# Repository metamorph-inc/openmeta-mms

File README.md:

# OpenMETA Source Repository #
OpenMETA is an integrated, open-source, model-based platform used to design and analyze complex systems, such as spacecraft, automobiles, aircraft, and electronics.

This repository is a fork of OpenMETA that includes extensions developed by MetaMorph, Inc.

The core OpenMETA codebase is available here:
https://github.com/metamorph-inc/meta-core

## Obtaining OpenMETA
The easiest way to get started with OpenMETA is to download an installer for Windows. OpenMETA installers for Windows are frequently released by MetaMorph, Inc at their website:
https://openmeta.metamorphsoftware.com/

To build OpenMETA from source, see **[BUILD.md](BUILD.md)**.

## Documentation and Examples
User documentation for OpenMETA is hosted by MetaMorph, Inc at:
http://docs.metamorphsoftware.com 

The documentation includes:
* Concept Introduction
* Walkthroughs
* Details of specific tool integrations

Case Studies
* OpenMETA for Electronics Design
  * Live Presentation and Demonstration: https://www.youtube.com/watch?v=KghND-sZ0s4
* Vahana Trade Study _(aerospace)_. Autonomous transport vehicle.
  * Report: https://www.metamorphsoftware.com/blog/2017/8/31/openmeta-vahana-case-study-part-i
  * Project: https://github.com/metamorph-inc/openmeta-vahana
* Spacecraft Trade Study
  * Quick Tour Video: https://www.youtube.com/watch?v=OHrgiL06z2s
  * Project: https://github.com/metamorph-inc/openmeta-spacecraft-study

## License
OpenMETA is distributed under the MIT open-source license. See **[license.txt](license.txt)**

This repository is a fork of OpenMETA that includes extensions developed by MetaMorph, Inc.

The core OpenMETA codebase is available here:
https://github.com/metamorph-inc/meta-core

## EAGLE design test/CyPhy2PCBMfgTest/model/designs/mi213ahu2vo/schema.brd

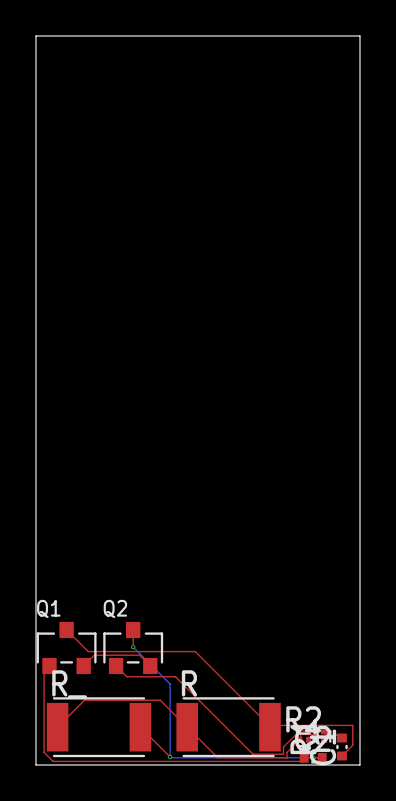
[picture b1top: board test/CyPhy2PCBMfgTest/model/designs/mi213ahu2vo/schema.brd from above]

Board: 2 copper layers, 18.0 x 40.5 mm, 8 parts (0 on the bottom side), 6 nets.

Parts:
C1, C2: C0402
Q1, Q2: TRANSISTOR_NPN_SOT23; SOT23
R: RESISTOR_2010; R_2010
R1, R2: RESISTOR_0201; R_0201
R_: RESISTOR_2010; R_2010

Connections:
unnamed: C2.1, Q1.B, R2.P$2
unnamed: C2.2, Q2.C, R_.P$2
unnamed: R.P$1, R1.P$1, R2.P$1, R_.P$1
unnamed: C1.2, Q2.B, R1.P$2
unnamed: C1.1, Q1.C, R.P$2
unnamed: Q1.E, Q2.E

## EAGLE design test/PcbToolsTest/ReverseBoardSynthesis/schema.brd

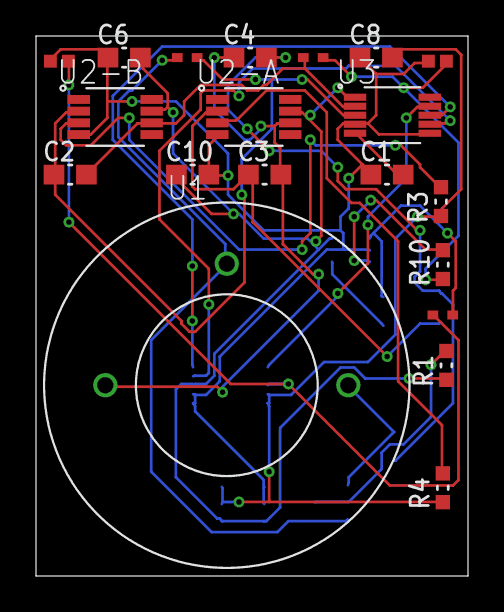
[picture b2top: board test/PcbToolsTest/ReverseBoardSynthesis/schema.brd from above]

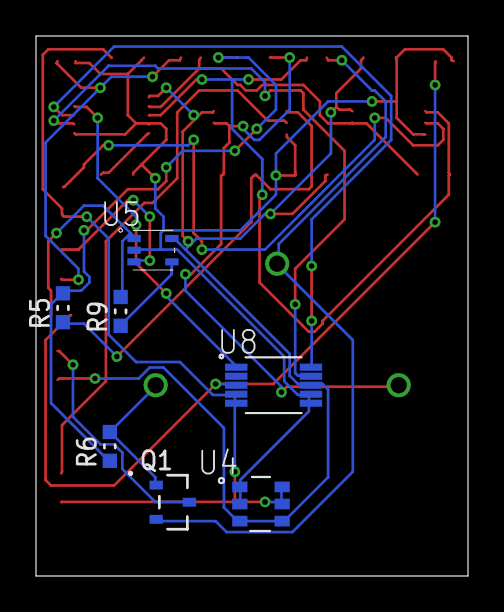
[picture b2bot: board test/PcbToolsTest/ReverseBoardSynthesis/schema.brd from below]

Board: 2 copper layers, 24.0 x 30.0 mm, 27 parts (7 on the bottom side), 22 nets.

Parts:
C1, C6: TMK107B7105KA-T; C_0603
C2, C3, C4: CL10B203KB8NNNC; C_0603
C8, C10: GCM188R71E104KA57D; C_0603
C9: C1005X5R0J106M050BC; C_0402
C14: CL05B562KB5NNNC; C_0402
Q1: MMBFJ270; SOT23-3
R1: CR0603-JW-105ELF; R_0603
R2: ERJ-2GEJ330X; R_0402
R3, R4, R5, R6: RT0603DRD0712K4L; R_0603
R8: ESR01MZPJ104; R_0402
R9, R10: CRCW06033K30JNEA; R_0603
R12: ERJ-2GEJ151X; R_0402
U1: CO-AX
U2-A, U2-B: ADA4528-2ARMZ; MSOP-8
U3: AD5270BRMZ-20; MSOP-10
U4: AD3412ARJZ; SOT-23
U5: AD8500AKSZ-R2; SC-70
U8: AD7790BRMZ; MSOP-10

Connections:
unnamed: C1.1, C6.1, C8.1, C9.1, C10.2, C14.1, U2-A.P$4, U2-B.P$4, U3.P$4, U3.P$6, U4.P$1, U4.P$2, U5.P$2, U8.P$6, U8.P$7
unnamed: C1.2, U3.P$5
unnamed: C6.2, C10.1, R1.P$1, U2-A.P$7, U2-B.P$7, U3.P$1, U4.P$3, U4.P$4, U5.P$5, U8.P$8
unnamed: C14.2, R12.P$1, U8.P$3
unnamed: C2.2, R8.P$1, U2-B.P$6, U3.P$2
unnamed: C2.1, R2.P$2, U2-B.P$2, U3.P$3
unnamed: C3.2, C4.1, U1.COUNTER, U2-A.P$6
unnamed: C3.1, R5.P$1, U2-A.P$2
unnamed: C4.2, R5.P$2, R6.P$1
unnamed: C8.2, R3.P$1, R4.P$1, U4.P$5, U4.P$6, U8.P$4, U8.P$5
unnamed: C9.2, R8.P$2, R10.P$1
unnamed: Q1.1, R6.P$2, U1.REFERENCE
unnamed: Q1.2, R2.P$1, U1.WORKER
unnamed: Q1.3, R1.P$2
unnamed: R10.P$2, U5.P$3
unnamed: R9.P$2, R12.P$2, U5.P$1
unnamed: R3.P$2, U2-B.P$3
unnamed: R4.P$2, U2-A.P$3
unnamed: R9.P$1, U5.P$4
unnamed: U3.P$9, U8.P$1
unnamed: U3.P$8, U8.P$10
unnamed: U3.P$7, U8.P$9

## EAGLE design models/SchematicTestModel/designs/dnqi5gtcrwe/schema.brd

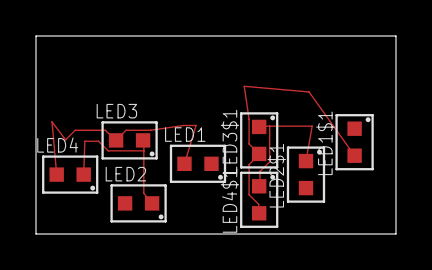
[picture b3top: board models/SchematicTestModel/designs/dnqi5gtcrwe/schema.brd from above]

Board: 2 copper layers, 20.0 x 11.0 mm, 8 parts (0 on the bottom side), 4 nets.

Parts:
LED1, LED1$1, LED2, LED2$1, LED3, LED3$1, LED4, LED4$1: LTST-C191KRKT; LED

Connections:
unnamed: LED2.CATHODE, LED3.CATHODE, LED4.CATHODE
unnamed: LED1.ANODE, LED3.ANODE, LED4.ANODE
unnamed: LED2$1.CATHODE, LED3$1.CATHODE, LED4$1.CATHODE
unnamed: LED1$1.ANODE, LED3$1.ANODE, LED4$1.ANODE

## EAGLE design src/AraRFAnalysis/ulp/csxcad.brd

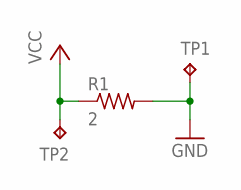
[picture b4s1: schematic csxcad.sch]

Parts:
R1: 2; R0603
TP1, TP2: TPB2,54; B2,54

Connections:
GND: R1.2, TP1.TP
VCC: R1.1, TP2.TP

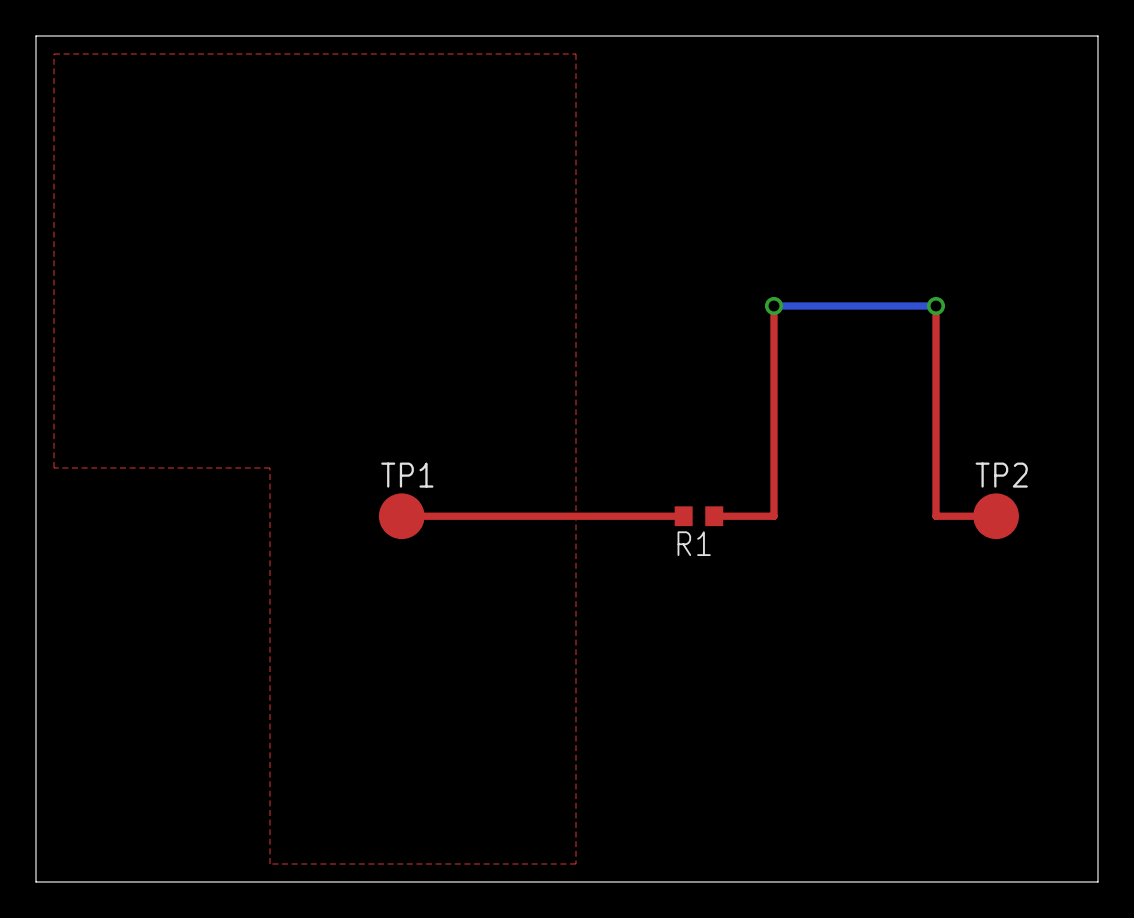
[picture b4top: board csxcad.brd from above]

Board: 2 copper layers, 59.0 x 47.0 mm, 3 parts (0 on the bottom side), 2 nets.

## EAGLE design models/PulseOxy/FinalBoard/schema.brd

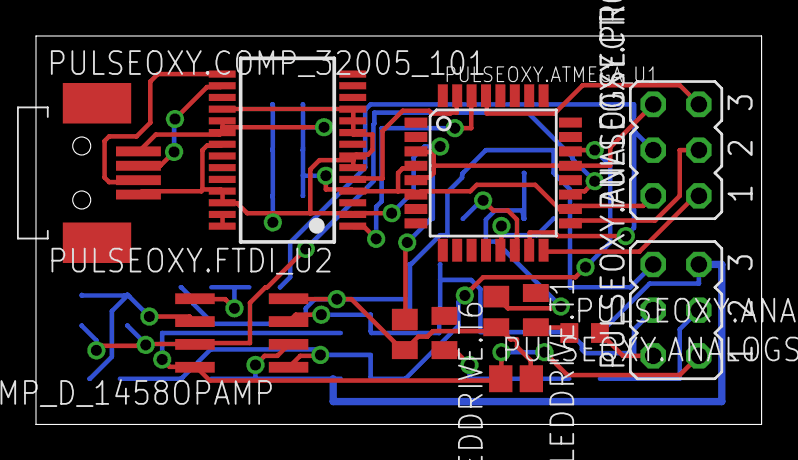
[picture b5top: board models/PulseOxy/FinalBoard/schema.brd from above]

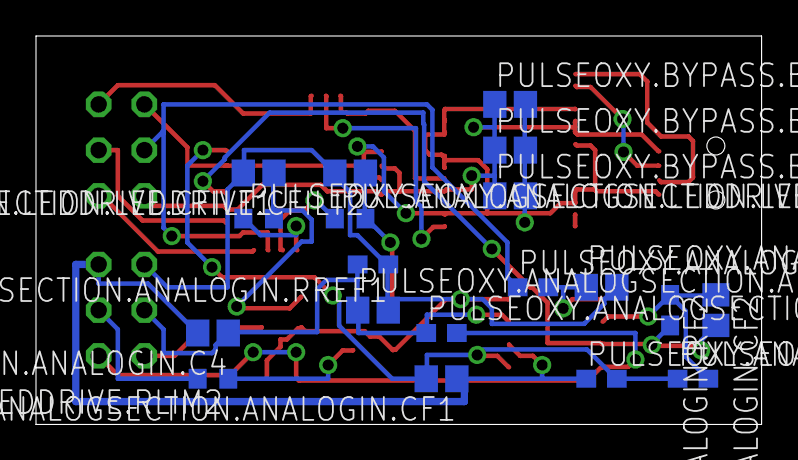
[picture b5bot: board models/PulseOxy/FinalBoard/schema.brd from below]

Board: 2 copper layers, 40.3 x 21.6 mm, 29 parts (19 on the bottom side), 27 nets.

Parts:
PULSEOXY.ANALOGSECTION.ANALOGIN.C2, PULSEOXY.ANALOGSECTION.ANALOGIN.C4, PULSEOXY.ANALOGSECTION.ANALOGIN.CBP1, PULSEOXY.ANALOGSECTION.ANALOGIN.CF1, PULSEOXY.ANALOGSECTION.ANALOGIN.CF2, PULSEOXY.ANALOGSECTION.ANALOGIN.CREF, PULSEOXY.ANALOGSECTION.LEDDRIVE.CFILT1, PULSEOXY.ANALOGSECTION.LEDDRIVE.CFILT2, PULSEOXY.BYPASS.BP1, PULSEOXY.BYPASS.BP2, PULSEOXY.BYPASS.BP3: C0805
PULSEOXY.ANALOGSECTION.ANALOGIN.COMP_D_1458OPAMP: LM1458D; SO08
PULSEOXY.ANALOGSECTION.ANALOGIN.R11, PULSEOXY.ANALOGSECTION.ANALOGIN.RF1, PULSEOXY.ANALOGSECTION.ANALOGIN.RF2, PULSEOXY.ANALOGSECTION.ANALOGIN.RI2, PULSEOXY.ANALOGSECTION.ANALOGIN.RREF1, PULSEOXY.ANALOGSECTION.ANALOGIN.RREF2: C0603
PULSEOXY.ANALOGSECTION.LEDDRIVE.RDRIVE1, PULSEOXY.ANALOGSECTION.LEDDRIVE.RDRIVE2, PULSEOXY.ANALOGSECTION.LEDDRIVE.RLIM1, PULSEOXY.ANALOGSECTION.LEDDRIVE.RLIM2: R0603
PULSEOXY.ANALOGSECTION.LEDDRIVE.T1, PULSEOXY.ANALOGSECTION.LEDDRIVE.T6: SOT143
PULSEOXY.ANALOGSECTION.SENSORHEADER, PULSEOXY.PROGRPORT: JP3Q
PULSEOXY.ATMEGA_U1: MEGA48/88/168-AU; TQFP32-08
PULSEOXY.COMP_32005_101: MINI-USB_4P-32005-101; 32005-101
PULSEOXY.FTDI_U2: FT232RL; SSOP28

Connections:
unnamed: PULSEOXY.ANALOGSECTION.ANALOGIN.C2.2, PULSEOXY.ANALOGSECTION.ANALOGIN.CBP1.2, PULSEOXY.ANALOGSECTION.ANALOGIN.COMP_D_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.4, PULSEOXY.ANALOGSECTION.ANALOGIN.CREF.2, PULSEOXY.ANALOGSECTION.ANALOGIN.RREF1.1, PULSEOXY.ANALOGSECTION.LEDDRIVE.CFILT1.2, PULSEOXY.ANALOGSECTION.LEDDRIVE.CFILT2.2, PULSEOXY.ANALOGSECTION.LEDDRIVE.T1.2, PULSEOXY.ANALOGSECTION.LEDDRIVE.T6.2, PULSEOXY.ANALOGSECTION.SENSORHEADER.6
unnamed: PULSEOXY.ANALOGSECTION.ANALOGIN.C2.1, PULSEOXY.ANALOGSECTION.ANALOGIN.COMP_D_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.5, PULSEOXY.ANALOGSECTION.ANALOGIN.R11.2
unnamed: PULSEOXY.ANALOGSECTION.ANALOGIN.C4.2, PULSEOXY.ANALOGSECTION.ANALOGIN.CF1.1, PULSEOXY.ANALOGSECTION.ANALOGIN.COMP_D_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.2, PULSEOXY.ANALOGSECTION.ANALOGIN.RF1.1, PULSEOXY.ANALOGSECTION.SENSORHEADER.5
unnamed: PULSEOXY.ANALOGSECTION.ANALOGIN.C4.1, PULSEOXY.ANALOGSECTION.ANALOGIN.COMP_D_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.3, PULSEOXY.ANALOGSECTION.ANALOGIN.CREF.1, PULSEOXY.ANALOGSECTION.ANALOGIN.RREF1.2, PULSEOXY.ANALOGSECTION.ANALOGIN.RREF2.1, PULSEOXY.ANALOGSECTION.SENSORHEADER.4
unnamed: PULSEOXY.ANALOGSECTION.ANALOGIN.CBP1.1, PULSEOXY.ANALOGSECTION.ANALOGIN.COMP_D_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.8, PULSEOXY.ANALOGSECTION.ANALOGIN.RREF2.2, PULSEOXY.ANALOGSECTION.SENSORHEADER.1
unnamed: PULSEOXY.ANALOGSECTION.ANALOGIN.CF1.2, PULSEOXY.ANALOGSECTION.ANALOGIN.COMP_D_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.1, PULSEOXY.ANALOGSECTION.ANALOGIN.RF1.2, PULSEOXY.ANALOGSECTION.ANALOGIN.RI2.1, PULSEOXY.ATMEGA_U1.22
unnamed: PULSEOXY.ANALOGSECTION.ANALOGIN.CF2.2, PULSEOXY.ANALOGSECTION.ANALOGIN.COMP_D_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.7, PULSEOXY.ANALOGSECTION.ANALOGIN.RF2.2, PULSEOXY.ATMEGA_U1.19
unnamed: PULSEOXY.ANALOGSECTION.ANALOGIN.CF2.1, PULSEOXY.ANALOGSECTION.ANALOGIN.COMP_D_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.6, PULSEOXY.ANALOGSECTION.ANALOGIN.RF2.1, PULSEOXY.ANALOGSECTION.ANALOGIN.RI2.2
unnamed: PULSEOXY.ANALOGSECTION.ANALOGIN.R11.1, PULSEOXY.ATMEGA_U1.15, PULSEOXY.PROGRPORT.4
unnamed: PULSEOXY.ANALOGSECTION.LEDDRIVE.CFILT1.1, PULSEOXY.ANALOGSECTION.LEDDRIVE.RDRIVE1.2, PULSEOXY.ANALOGSECTION.LEDDRIVE.T1.1
unnamed: PULSEOXY.ANALOGSECTION.LEDDRIVE.CFILT2.1, PULSEOXY.ANALOGSECTION.LEDDRIVE.RDRIVE2.2, PULSEOXY.ANALOGSECTION.LEDDRIVE.T6.1
unnamed: PULSEOXY.ANALOGSECTION.LEDDRIVE.RDRIVE1.1, PULSEOXY.ATMEGA_U1.13
unnamed: PULSEOXY.ANALOGSECTION.LEDDRIVE.RDRIVE2.1, PULSEOXY.ATMEGA_U1.14
unnamed: PULSEOXY.ANALOGSECTION.LEDDRIVE.RLIM1.2, PULSEOXY.ANALOGSECTION.SENSORHEADER.2
unnamed: PULSEOXY.ANALOGSECTION.LEDDRIVE.RLIM1.1, PULSEOXY.ANALOGSECTION.LEDDRIVE.T1.3
unnamed: PULSEOXY.ANALOGSECTION.LEDDRIVE.RLIM2.1, PULSEOXY.ANALOGSECTION.LEDDRIVE.T6.3
unnamed: PULSEOXY.ANALOGSECTION.LEDDRIVE.RLIM2.2, PULSEOXY.ANALOGSECTION.SENSORHEADER.3
unnamed: PULSEOXY.ATMEGA_U1.4, PULSEOXY.ATMEGA_U1.6, PULSEOXY.ATMEGA_U1.18, PULSEOXY.BYPASS.BP1.1, PULSEOXY.BYPASS.BP2.1, PULSEOXY.BYPASS.BP3.1, PULSEOXY.COMP_32005_101.1, PULSEOXY.FTDI_U2.4, PULSEOXY.FTDI_U2.19, PULSEOXY.FTDI_U2.20, PULSEOXY.PROGRPORT.2
unnamed: PULSEOXY.ATMEGA_U1.3, PULSEOXY.ATMEGA_U1.5, PULSEOXY.ATMEGA_U1.21, PULSEOXY.BYPASS.BP1.2, PULSEOXY.BYPASS.BP2.2, PULSEOXY.BYPASS.BP3.2, PULSEOXY.COMP_32005_101.4, PULSEOXY.FTDI_U2.2, PULSEOXY.FTDI_U2.6, PULSEOXY.FTDI_U2.7, PULSEOXY.FTDI_U2.9, PULSEOXY.FTDI_U2.10, PULSEOXY.FTDI_U2.11, PULSEOXY.FTDI_U2.18, PULSEOXY.FTDI_U2.21, PULSEOXY.FTDI_U2.25, PULSEOXY.FTDI_U2.26, PULSEOXY.PROGRPORT.6
unnamed: PULSEOXY.ATMEGA_U1.30, PULSEOXY.FTDI_U2.1
unnamed: PULSEOXY.ATMEGA_U1.31, PULSEOXY.FTDI_U2.5
unnamed: PULSEOXY.ATMEGA_U1.29, PULSEOXY.PROGRPORT.5
unnamed: PULSEOXY.ATMEGA_U1.16, PULSEOXY.PROGRPORT.1
unnamed: PULSEOXY.ATMEGA_U1.17, PULSEOXY.PROGRPORT.3
unnamed: PULSEOXY.COMP_32005_101.3, PULSEOXY.FTDI_U2.15
unnamed: PULSEOXY.COMP_32005_101.2, PULSEOXY.FTDI_U2.16
unnamed: PULSEOXY.FTDI_U2.27, PULSEOXY.FTDI_U2.28

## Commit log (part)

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2017-11-21 Update Python dependencies (for MATLAB bare file support)
2017-11-22 OPENMETA-329 Added table of conversions to MATLAB docs.
2017-11-27 OPENMETA-329 Added CSS fix for 'code-block' caption permalinks.
2017-11-29 OPENMETA-332 add documentation for including and excluding specific test benches with the Continuous Integration script
2017-11-29 RunTestBenches: support PETs
2017-11-30 RunTestBenches: check PET MetricConstraints in all hierarchy and all runs
2017-11-30 OPENMETA-335 Updated MATLAB/OpenMDAO mapping table.
2017-12-01 Updated Continuous Integration Docs.
2017-12-04 Remote execution skeleton code
2017-12-07 More implementation of remote job mananger support; test project for remote job manager support (and placeholder for other PET tests)
2017-12-11 OPENMETA-346 Start Adding CAD Documentation.
2017-12-11 OPENMETA-346 Finish initial cut at CAD Documentation.
2017-12-13 Fix broken links to documentation in BUILD.md
2017-12-13 SimulinkImporter test fixture: don't crash if MATLAB isn't installed
2017-12-14 Prompt for remote server username and password
2017-12-14 UI tweak to remote server dialog
2017-12-15 Add CATIA to CADModel.FileFormat
2018-01-02 OPENMETA-357 General cleanup of existing code.
2018-01-03 OPENMETA-357 Fix naming convention of functions.
2018-01-03 OPENMETA-357 Fix xunit reference errors.
2018-01-04 OPENMETA-357 Set Abort to false in InvokeEx.
2018-01-05 OPENMETA-357 Added new Merge Connectors code.
2018-01-05 OPENMETA-357 Fixed Merge behaviour.
2018-01-05 Consider any 'complete' status where _FAILED.txt is present to be a failure (matches LocalPool behavior); reorder status check so that Test Benches tab updates after we've downloaded results
2018-01-08 OPENMETA-357 Refactored SpiceImportWithPinMatch() test.
    1. Reverted ComponentAuthoringTool.xme.
    2. Added Generator library and device.
    3. Import generator device before spice import.
2018-01-09 OPENMETA-349 Improvements to CustomProcessor.py
2018-01-10 OPENMETA-360 Recently used server list in remote server connection dialog
2018-01-12 OPENMETA-349 Added documentation for Custom Processor.
2018-01-12 OPENMETA-348 Add picture of CSV File DOE Type Configuration.
2018-01-12 Populate remote job labels with labels from interpreters
2018-01-13 OPENMETA-349 Added new operators to ValueAggregator.py
    Added COUNT, AVERAGE, MIN, MAX, AND, OR
    Augmented the documentation to include the new operators.
2018-01-15 Fixed preparepublish.bat script to point to META Python.
2018-01-19 OPENMETA-362 Use Python path from registry for Simulink test bench execution
2018-01-22 TestRemoteExecution: don't depend on xunit, it is not in the installer. OPENMETA-384
2018-01-22 TestRemoteExecution: add more labels
2018-01-23 OPENMETA-391 Add SPICETest TB to SchematicUnitTests.
2018-01-23 Upgrade to v2.0.0 of openmeta-visualizer.
2018-01-23 OPENMETA-356 Handle remote executor cancellation requested status
2018-01-24 OPENMETA-371 Added sections on Job Labels and Remote Job Statuses.
2018-01-25 One more case where a right-click item could be invoked with no selected item
2018-01-26 OPENMETA-371 some formatting on Test Benches first page
2018-01-26 OPENMETA-371 Updated definitions of test bench.
2018-01-30 Add tonka-specific Jenkinsfile
2018-01-30 Changed docs to draw version number from git tag.
2018-01-31 Use full artifact path for unarchive command
2018-01-31 Adjust cache behavior on root website objects
2018-01-31 Psuedo-release 0.18.2
2018-02-01 OPENMETA-410 Change ToC title from 'Caption' to 'Sections'.
2018-02-01 docs/make: Fail on error
2018-02-01 Fix syntax of s3Upload command
2018-02-01 Use path without / prefix to delete and upload docs
2018-02-05 OPENMETA-413 Added new docs chapters into index.
2018-02-06 OPENMETA-413 Fix broken master interpreter reference.
2018-02-06 OPENMETA-413 Some minor changes to docs to prepare stubs for contributions.
2018-02-07 OPENMETA-418 Initial draft for OpenMETA projects Chapter.
2018-02-08 OPENMETA-425 Master Interpreter Docs
2018-02-08 OPENMETA-426 Create new See It In Action chapter. Move Hello World.
2018-02-09 OPENMETA-417 Completed Hello World tutorial and added hello_world OpenMETA project.
2018-02-09 Testbenches: re-add Workflows under 'AraTestBenches' since some models depend on them
2018-02-09 CyPhy2MfgBom: properly close log file instead of relying on finalizer
2018-02-09 OPENMETA-420 Move Component Composition section to Component Assemblies chapter.
2018-02-09 Don't need matlab.pth; MATLAB python is added by matlab_wrapper
2018-02-12 OPENMETA-430 Switching to using menuselection directive.
2018-02-12 Fixed typos found in OpenMETA Projects chapter & added a more detailed description of the example .gitignore file
2018-02-14 Corrected Typos and clarified some wording in LED Tutorial, Components, Design Spaces, Domains, and Interpreters chapters
2018-02-16 Fixed typos and a naming issue in PET Tutorial
2018-02-16 Typos and wording corrected in Utilities chapter
2018-02-19 OPENMETA-422 Added note about enabling interpreter buttons.
2018-02-19 Added clarification to LED Tutorial and fixed typos in Integrated Domain section
2018-02-20 OPENMETA-338 Adjust docs to reflect tested MATLAB compatibility.
2018-02-20 OPENMETA-417 Revert a couple small changes.
2018-02-21 Changed all 'Contents:' to 'Sections'
2018-02-21 OPENMETA-417 Renamed test bench references/links.
2018-02-21 OPENMETA-417 Fixed broken link.
2018-02-21 OPENMETA-423 Revised Test Bench chapter of documentation.
2018-02-21 OPEMNETA-419 add tutorial on Class Inheritance for Component Authoring
2018-02-23 Updated final few PET Tutorial Screenshots and fixed a broken reference in OpenMETA Projects
2018-02-23 OPENMETA-423 Fixed typos in Test Benches chapter
2018-02-26 OPENMETA-419 Updated images in Inheritance tutorial to comply with Documentation style guide
2018-02-26 Fixed typos throughout, and clarified sections of the FEA tutorial in Integrated Domains
2018-02-27 OPENMETA-417 added missing reference anchor link.
2018-02-28 Jenkins: only build CAD if it is not on nuget
2018-02-28 OPENMETA-416 Images updated and clarification added in PET Reference
2018-03-02 OPENMETA-428 Fixed broken sentence regarding Python wrappers in PET Reference
2018-03-02 OPENMETA-428 Duplicated conceptual LED Component drawing in the Components chapter for clarity
2018-03-02 OPENMETA-428 Fixed references to the FEA tutorial example files
2018-03-28 Remove dup pywin32
2018-03-29 Port over old PCC docs (without images for now)
2018-03-30 Rename installer for easier version tracking
2018-04-04 OPENMETA-485 Minor formatting changes.
2018-04-04 More icons and layout fixes
2018-04-05 API changes to allow CAT modules to support execution within ComponentAssemblies
2018-04-05 Fix SchematicUnitTests to use new CAT tool API
2018-04-05 Remove unused CAT icons
2018-04-06 Put some tonka Python packages into zip for installer
2018-04-11 Update copyright dates
2018-04-25 CyPhy2Schematic: add onlyConsiderExactConstraints workflow option
2018-06-08 Add library picker to Simulink CAT
2018-06-13 OPENMETA-476 Check that results folders exist before attempting to watch them for changes when launching visualizer
2018-06-22 Release notes for v0.18.5
2018-06-26 Don't do checkout -b master since the branch already exists and Git apparently doesn't like it when you do that
2018-06-26 Addition of Included Tools section.
2018-06-26 Further improved Installation instructions.
2018-06-27 OPENMETA-517 Prepare for 0.18.6 release.
2018-06-27 Update to point to new OpenMETA homepage
2018-06-28 OPENMETA-517 Constrain images sizes on installation page.
2018-06-28 Release notes for v0.18.7.
2018-07-12 OPENMETA-528 Make PETBrowser SingleInstanceManager per-user
2018-07-27 OPENMETA-530 Show open dialog if there's no results folder to load at the selected location
2018-07-30 OPENMETA-537 Restructured Analysis Blocks Chapters.
2018-08-28 Release notes for v0.19.1.
2018-10-02 Modify documentation to reflect new OpenModelica version (1.12) OPENMETA-558
2018-10-16 Fix botched merge
2018-10-26 Some minor documentation improvements and typo fixes.
2018-10-26 Added another entry to release notes.
2018-11-21 remote_execution /build/: accept job names with dashes
2019-01-04 Add mgardf
2019-01-08 Release v0.21.1; repackaging 0.21.0 due to issue with merge commit on release branch
2019-02-04 Revert accidental change to paraboloid.py
2019-04-23 Remove CyPhy2MfgBom from docs
2019-07-02 Decorator: look for icons where libraries are. OPENMETA-615
2019-07-03 Correct company name in license
2019-09-13 Add one more thing to 0.21.3 release notes
2019-09-16 run_mdao: add --profile command line flag (enables OpenMDAO instance-based profiling)
2019-11-02 Bump request from 2.33.0 to 2.88.0 in /bin/cad.js
    Bumps [request](https://github.com/request/request) from 2.33.0 to 2.88.0.
    - [Release notes](https://github.com/request/request/releases)
    - [Changelog](https://github.com/request/request/blob/master/CHANGELOG.md)
    - [Commits](https://github.com/request/request/compare/v2.33.0...v2.88.0)
2020-01-29 Upgrade to OpenMETA Visualizer v2.1.8.
2020-02-17 Revert "OPENMETA-677 Normalize PYTHONPATH and PYTHONHOME when running jobs in job manager"
    This reverts commit f6d11a2a7198d5a2a4709d7ca9e9fec48a576321.
2020-02-24 Partially functional progress feedback server
2020-02-26 Fix unintentional commit of unresolved conflicted requirements file
2020-02-26 Document progress feedback service protocol; add dependencies to THIRD_PARTY.md
2020-02-29 Upgrade to Visualizer v2.1.10
2020-03-04 Add unsaved release notes
2020-03-30 Set GenericDomainModelParameter icon and portIcon. OPENMETA-717
2020-04-13 Add visualizer export scripts
2020-04-27 Update Meta-Link Java-dependency information
2020-05-05 Fix CyPhy2PCBMfg relying on current working directory
2020-05-21 Allow exported visualizer packages to run under visualizer when installed per-user
2020-07-02 Add list of PET folders to results browser, and ability to navigate directly to them
2020-08-20 Bump bcrypt from 1.0.2 to 5.0.0 in /src/remote_execution
    Bumps [bcrypt](https://github.com/kelektiv/node.bcrypt.js) from 1.0.2 to 5.0.0.
    - [Release notes](https://github.com/kelektiv/node.bcrypt.js/releases)
    - [Changelog](https://github.com/kelektiv/node.bcrypt.js/blob/master/CHANGELOG.md)
    - [Commits](https://github.com/kelektiv/node.bcrypt.js/compare/v1.0.2...v5.0.0)
2020-11-25 Add temporary notice regarding Autodesk EAGLE
2021-03-29 v0.23.0 release notes (WIP)
2021-04-02 Added GME update to release notes
2021-04-26 Bump commons-io from 2.4 to 2.7 in /src/MetaLink/meta-bridge
    Bumps commons-io from 2.4 to 2.7.
2021-06-07 Bump logback-classic from 1.0.13 to 1.2.0 in /src/MetaLink/meta-bridge
    Bumps logback-classic from 1.0.13 to 1.2.0.
    ---
    updated-dependencies:
    - dependency-name: ch.qos.logback:logback-classic
    dependency-type: direct:production
    ...
2021-08-17 Upgrade pywin32 to v228
2021-08-19 Disable Octopart tests to prevent maxing out api uses
2021-09-17 Fix some sprintf buffer lengths and formats
2022-01-05 Add v0.24.0 release notes
2022-01-07 Bump protobuf-java from 2.6.1 to 3.16.1 in /src/MetaLink/meta-protobuf
    Bumps [protobuf-java](https://github.com/protocolbuffers/protobuf) from 2.6.1 to 3.16.1.
    - [Release notes](https://github.com/protocolbuffers/protobuf/releases)
    - [Changelog](https://github.com/protocolbuffers/protobuf/blob/master/generate_changelog.py)
    - [Commits](https://github.com/protocolbuffers/protobuf/compare/v2.6.1...v3.16.1)
    ---
    updated-dependencies:
2022-10-04 Bump protobuf-java from 2.6.1 to 3.16.3 in /src/MetaLink/meta-protobuf
    Bumps [protobuf-java](https://github.com/protocolbuffers/protobuf) from 2.6.1 to 3.16.3.
    - [Release notes](https://github.com/protocolbuffers/protobuf/releases)
    - [Changelog](https://github.com/protocolbuffers/protobuf/blob/main/generate_changelog.py)
    - [Commits](https://github.com/protocolbuffers/protobuf/compare/v2.6.1...v3.16.3)
    ---
    updated-dependencies:
2023-01-13 Use .NET Framework 4.6.2
2023-01-16 Fix test for nondeterministic xml attribute order
2023-03-03 Component exporter: fix GenericDomainModelPort PortComposition going Connector->GenericDomainModel
2023-03-08 Add v0.24.1 release notes
2023-03-21 Generate *.cir without running ngspice
